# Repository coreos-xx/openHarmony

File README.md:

# Open Harmony OnstepX controller

A custom onstepx PCB for the open harmony mounts featuring a Teensy 4.0 controller, 2xTMC2209 v3 stepper motor drivers, and an ESP32 S3 for the SWS interface

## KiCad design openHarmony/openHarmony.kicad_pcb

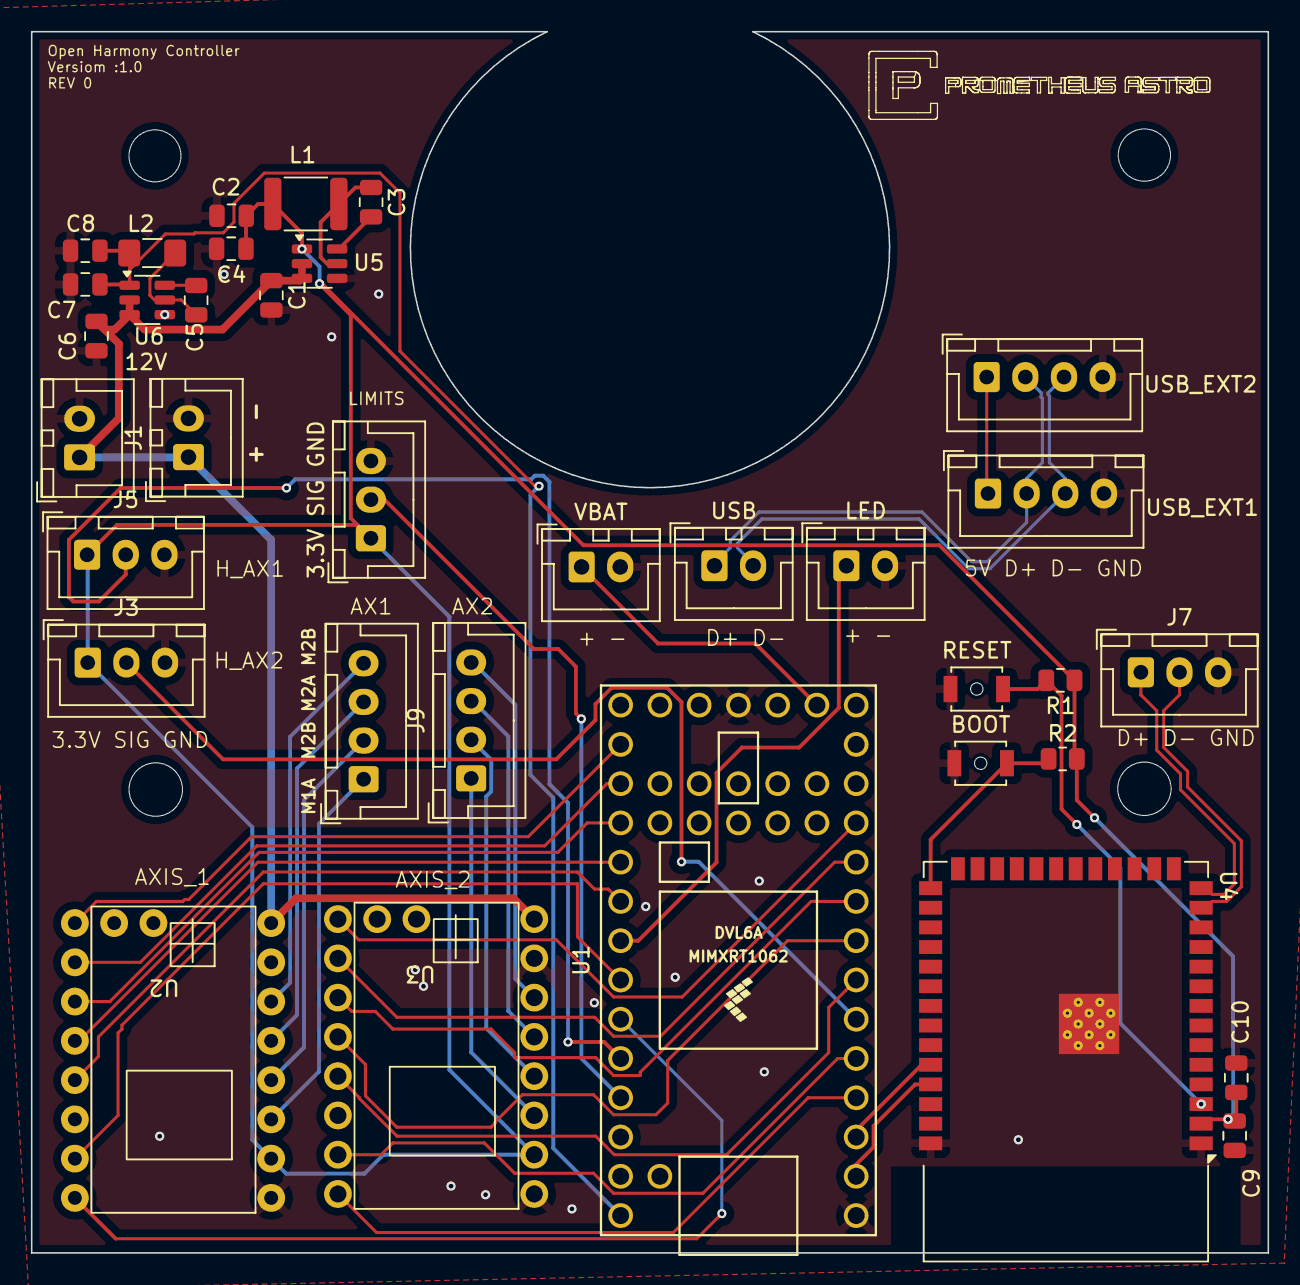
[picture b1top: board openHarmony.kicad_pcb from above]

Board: 2 copper layers, 80.0 x 79.0 mm, 35 parts (0 on the bottom side), 44 nets.

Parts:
3.3V SIG GND: LIMIT; JST_XH_B3B-XH-A_1x03_P2.50mm_Vertical
12V: 12V; JST_XH_B2B-XH-A_1x02_P2.50mm_Vertical
BOOT: SW_Boot; SW_SPST_B3U-1000P-B
C1, C6, C10: 10u; C_0805_2012Metric
C2, C4, C7, C8: 22u; C_0805_2012Metric
C3, C5, C9: 100n; C_0805_2012Metric
J1: 12V; JST_XH_B2B-XH-A_1x02_P2.50mm_Vertical
J3: Home1; JST_XH_B3B-XH-A_1x03_P2.50mm_Vertical
J5: Home2; JST_XH_B3B-XH-A_1x03_P2.50mm_Vertical
J7: ESP32Prog; JST_XH_B3B-XH-A_1x03_P2.50mm_Vertical
J9: Ax2; JST_XH_B4B-XH-A_1x04_P2.50mm_Vertical
L1: 3.9u; L_1812_4532Metric
L2: 4.7u; L_1206_3216Metric_Pad1.42x1.75mm_HandSolder
LED: LED; JST_XH_B2B-XH-A_1x02_P2.50mm_Vertical
M1A  M2B M2A M2B: Ax1; JST_XH_B4B-XH-A_1x04_P2.50mm_Vertical
R1, R2: R; R_0805_2012Metric
RESET: SW_Reset; SW_SPST_B3U-1000P-B
U1: Teensy4.0; Teensy40
U2, U3: TMC2130Stick
U4: ESP32-S3-WROOM-1
U5: AP63203WU; TSOT-23-6
U6: AP63205WU; TSOT-23-6
USB: UDB_INT; JST_XH_B2B-XH-A_1x02_P2.50mm_Vertical
USB_EXT1: USB_EXT; JST_XH_B4B-XH-A_1x04_P2.50mm_Vertical
USB_EXT2: USB_EXT2; JST_XH_B4B-XH-A_1x04_P2.50mm_Vertical
VBAT: bat; JST_XH_B2B-XH-A_1x02_P2.50mm_Vertical

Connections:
/3V3: 3.3V SIG GND.1, C2.1, C4.1, C9.1, C10.1, J3.1, J5.1, L1.2, R1.1, R2.2, U2.2 (VCC), U3.2 (VCC), U4.2 (3V3), U5.1 (FB)
/5V: C7.1, C8.1, L2.2, U1.33 (VIN), U6.1 (FB)
/5Vv: USB_EXT1.1, USB_EXT2.1
/AX1_M1A: M1A M2B M2A M2B.1, U2.3 (1A)
/AX1_M1B: M1A M2B M2A M2B.2, U2.4 (1B)
/AX1_M2A: M1A M2B M2A M2B.3, U2.5 (2A)
/AX1_M2B: M1A M2B M2A M2B.4, U2.6 (2B)
/AX2_M1A: J9.1, U3.3 (1A)
/AX2_M1B: J9.2, U3.4 (1B)
/AX2_M2A: J9.3, U3.5 (2A)
/AX2_M2B: J9.4, U3.6 (2B)
/CS1: U1.24 (17_A3_TX4_SDA1), U2.12 (CS)
/CS2: U1.8 (6_OUT1D), U3.12 (CS)
/D+: USB.1, USB_EXT1.2, USB_EXT2.2
/D-: USB.2, USB_EXT1.3, USB_EXT2.3
/DIR1: U1.28 (21_A7_RX5_BCLK1), U2.16 (Dir)
/DIR2: U1.4 (2_OUT2), U3.16 (Dir)
/EN1: U1.21 (14_A0_TX3_SPDIF_OUT), U2.9 (Enable)
/EN2: U1.11 (9_OUT1C), U3.9 (Enable)
/ESP_D+: J7.1, U4.14 (USB_D+)
/ESP_D-: J7.2, U4.13 (USB_D-)
/H1_SIG: J3.2, U1.6 (4_BCLK2)
/H2_SIG: J5.2, U1.29 (22_A8_CTX1)
/LED: LED.1, U1.26 (19_A5_SCL0)
/LIM_SIG: 3.3V SIG GND.2, U1.30 (23_A9_CRX1_MCLK1)
/MISO1: U1.25 (18_A4_SDA0), U2.13 (MISO/SDO)
/MISO2: U1.7 (5_IN2), U3.13 (MISO/SDO)
/MOSI1: U1.22 (15_A1_RX3_SPDIF_IN), U2.10 (MOSI/SDI)
/MOSI2: U1.10 (8_TX2_IN1), U3.10 (MOSI/SDI)
/RX1: U1.2 (0_RX1_CRX2_CS1), U4.37 (TXD0)
/SCK1: U1.23 (16_A2_RX4_SCL1), U2.11 (SCK)
/SCK2: U1.9 (7_RX2_OUT1A), U3.11 (SCK)
/STEP1: U1.27 (20_A6_TX5_LRCLK1), U2.15 (Step)
/STEP2: U1.5 (3_LRCLK2), U3.15 (Step)
/TX1: U1.3 (1_TX1_CTX2_MISO1), U4.36 (RXD0)
/VM: 12V.1, C1.1, C6.1, J1.1, U2.8 (VMOT), U3.8 (VMOT), U5.2 (EN), U5.3 (IN), U6.2 (EN), U6.3 (IN)
/Vbat: U1.15 (VBAT), VBAT.1
GND: 3.3V SIG GND.3, 12V.2, BOOT.1, C1.2, C2.2, C4.2, C6.2, C7.2, C8.2, C9.2, C10.2, J1.2, J3.3, J5.3, J7.3, LED.2, RESET.1, U1.1 (GND), U1.17 (GND), U2.1 (GND), U3.1 (GND), U3.7 (GND), U4.1 (GND), U4.40 (GND), U4.41 (GND), U5.4 (GND), U6.4 (GND), USB_EXT1.4, USB_EXT2.4, VBAT.2
unnamed: R1.2, RESET.2, U4.3 (EN)
unnamed: BOOT.2, R2.1, U4.27 (IO0)
unnamed: C3.2, U5.6 (BST)
unnamed: C3.1, L1.1, U5.5 (SW)
unnamed: C5.2, U6.6 (BST)
unnamed: C5.1, L2.1, U6.5 (SW)

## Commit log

2025-07-19 Remove backup zip files and update .gitignore
2025-08-21 Update README.md
    fixed some typos
2025-08-21 Update README.md
    added image
